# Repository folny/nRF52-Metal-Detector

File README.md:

# nRF52 Metal Detector

Test Video
https://www.youtube.com/watch?v=v60ftfW6UR0

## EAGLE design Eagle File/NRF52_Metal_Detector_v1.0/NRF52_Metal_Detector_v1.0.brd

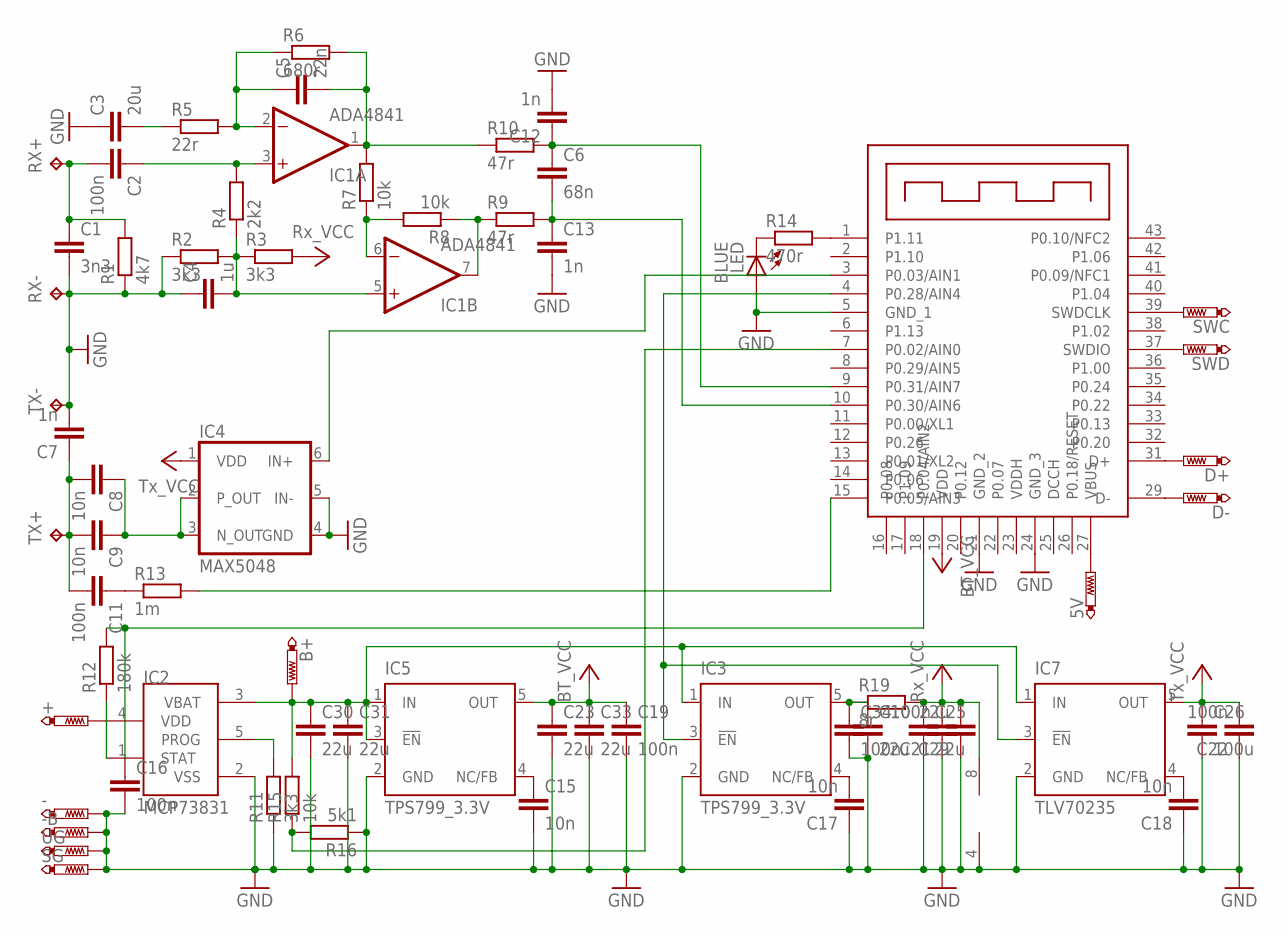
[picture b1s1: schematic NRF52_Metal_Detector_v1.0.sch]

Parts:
5V: PTR1TP13SQ; TP13SQ
+: PTR1TP20SQ; TP20SQ
-: PTR1TP20SQ; TP20SQ
-B: PTR1TP20SQ; TP20SQ
B+: PTR1TP20SQ; TP20SQ
C1: 3n3; C0805
C2, C11: 100n; C1206
C3: 20u; C1206
C4: 1u; C1206
C5: 22n; C0805
C6: 68n; C1206
C7, C12, C13: 1n; C0805
C8, C9: 10n; C1206
C10, C23, C25, C29, C30, C31, C33: 22u; C1206
C15, C17, C18: 10n; C0805
C16, C19, C21, C22, C34: 100n; C0805
C26: 100u; C1206
D+: PTR1TP13SQ; TP13SQ
D-: PTR1TP13SQ; TP13SQ
E73-2G4M08S1C1: E73-2G4M08S1C
IC1: ADA4841; SO08
IC2: MCP73831; SOT23-5L
IC3, IC5: TPS799_3.3V; SOT23-DBV
IC4: MAX5048; SOT23-6
IC7: TLV70235; SOT23-DBV
LED: BLUE; SML0805
R1: 4k7; R0805
R2, R3, R11: 3k3; R0805
R4: 2k2; R0805
R5: 22r; R0805
R6: 680r; R0805
R7, R8, R15: 10k; R0805
R9, R10: 47r; R0805
R12: 180k; R0805
R13: 1m; R0805
R14: 470r; R0805
R16: 5k1; R0805
R19: 8r; R1206
RX+: TPPAD1-13; P1-13
RX-: TPPAD1-13; P1-13
SG: PTR1TP13SQ; TP13SQ
SWC: PTR1TP13SQ; TP13SQ
SWD: PTR1TP13SQ; TP13SQ
TX+: TPPAD1-13; P1-13
TX-: TPPAD1-13; P1-13
UG: PTR1TP13SQ; TP13SQ

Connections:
+3V3A1: C10.1, C34.1, IC3.5 (OUT), R19.1
+3V3B: C19.1, C23.1, C33.1, E73-2G4M08S1C1.19 (VDD), IC5.5 (OUT)
+3V3T: C22.2, C26.1, IC4.1 (VDD), IC7.5 (OUT)
GND: -.TP, -B.TP, C1.2, C3.1, C4.1, C7.2, C10.2, C12.2, C13.2, C15.2, C16.2, C17.1, C18.1, C19.2, C21.1, C22.1, C23.2, C25.2, C26.2, C29.1, C30.2, C31.2, C33.2, C34.2, E73-2G4M08S1C1.5 (GND_1), E73-2G4M08S1C1.21 (GND_2), E73-2G4M08S1C1.24 (GND_3), IC1.4 (V-), IC2.2 (VSS), IC3.2 (GND), IC4.4 (GND), IC4.5 (IN-), IC5.2 (GND), IC7.2 (GND), LED.A, R1.1, R2.1, R11.1, R16.1, RX-.TP, SG.TP, TX-.TP, UG.TP
unnamed: C5.2, IC1.1 (OUT), R6.2, R7.2, R10.1
unnamed: C1.1, C2.2, R1.2, RX+.TP
unnamed: B+.TP, C30.1, C31.1, IC2.3 (VBAT), IC3.1 (IN), IC5.1 (IN), IC5.3 (!EN), IC7.1 (IN), R15.2
unnamed: C3.2, R5.1
unnamed: C5.1, IC1.2 (-IN), R5.2, R6.1
unnamed: C7.1, C8.2, C9.2, C11.2, TX+.TP
unnamed: E73-2G4M08S1C1.1 (P1.11), R14.2
unnamed: C2.1, IC1.3 (+IN), R4.2
unnamed: IC1.6 (-IN), R7.1, R8.2
unnamed: C17.2, IC3.4 (NC/FB)
unnamed: C15.1, IC5.4 (NC/FB)
unnamed: C6.2, C13.1, E73-2G4M08S1C1.10 (P0.30/AIN6), R9.2
unnamed: E73-2G4M08S1C1.39 (SWDCLK), SWC.TP
unnamed: E73-2G4M08S1C1.37 (SWDIO), SWD.TP
unnamed: +.TP, IC2.4 (VDD)
unnamed: IC2.5 (PROG), R11.2
unnamed: E73-2G4M08S1C1.4 (P0.28/AIN4), IC3.3 (!EN), IC7.3 (!EN)
unnamed: C16.1, E73-2G4M08S1C1.18 (P0.04/AIN2), R12.2
unnamed: C18.2, IC7.4 (NC/FB)
unnamed: IC2.1 (STAT), R12.1
unnamed: C8.1, C9.1, IC4.2 (P_OUT), IC4.3 (N_OUT)
unnamed: C11.1, R13.1
unnamed: E73-2G4M08S1C1.15 (P0.05/AIN3), R13.2
unnamed: LED.C, R14.1
unnamed: E73-2G4M08S1C1.7 (P0.02/AIN0), R15.1, R16.2
unnamed: C6.1, C12.1, E73-2G4M08S1C1.9 (P0.31/AIN7), R10.2
unnamed: E73-2G4M08S1C1.3 (P0.03/AIN1), IC4.6 (IN+)
unnamed: D+.TP, E73-2G4M08S1C1.31 (D+)
unnamed: D-.TP, E73-2G4M08S1C1.29 (D-)
unnamed: IC1.7 (OUT), R8.1, R9.1
unnamed: 5V.TP, E73-2G4M08S1C1.27 (VBUS)
unnamed: C4.2, IC1.5 (+IN), R2.2, R3.1, R4.1
RX_VCC: C21.2, C25.1, C29.2, IC1.8 (V+), R3.2, R19.2

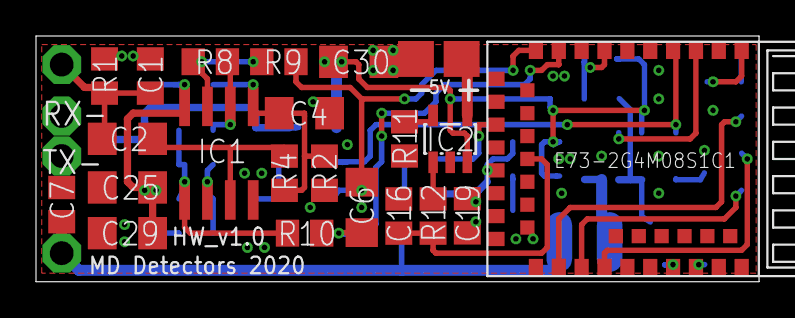
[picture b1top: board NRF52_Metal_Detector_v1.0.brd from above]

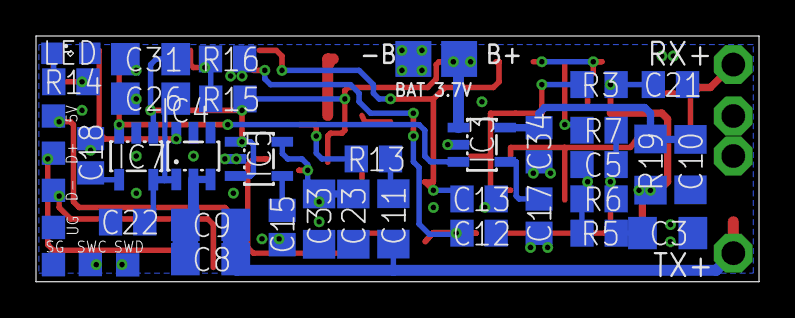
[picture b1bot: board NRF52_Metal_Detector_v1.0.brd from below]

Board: 2 copper layers, 40.2 x 13.7 mm, 68 parts (41 on the bottom side), 37 nets.

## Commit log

2020-05-18 Create Foto
2020-05-18 Create Info
2020-07-09 SDK
    SDK
2020-07-09 Project
2020-07-09 nRF5_Metal_Detector_SDK_15.3.0
2020-07-09 Add Eagle File
2020-07-09 Update Eagle Files
